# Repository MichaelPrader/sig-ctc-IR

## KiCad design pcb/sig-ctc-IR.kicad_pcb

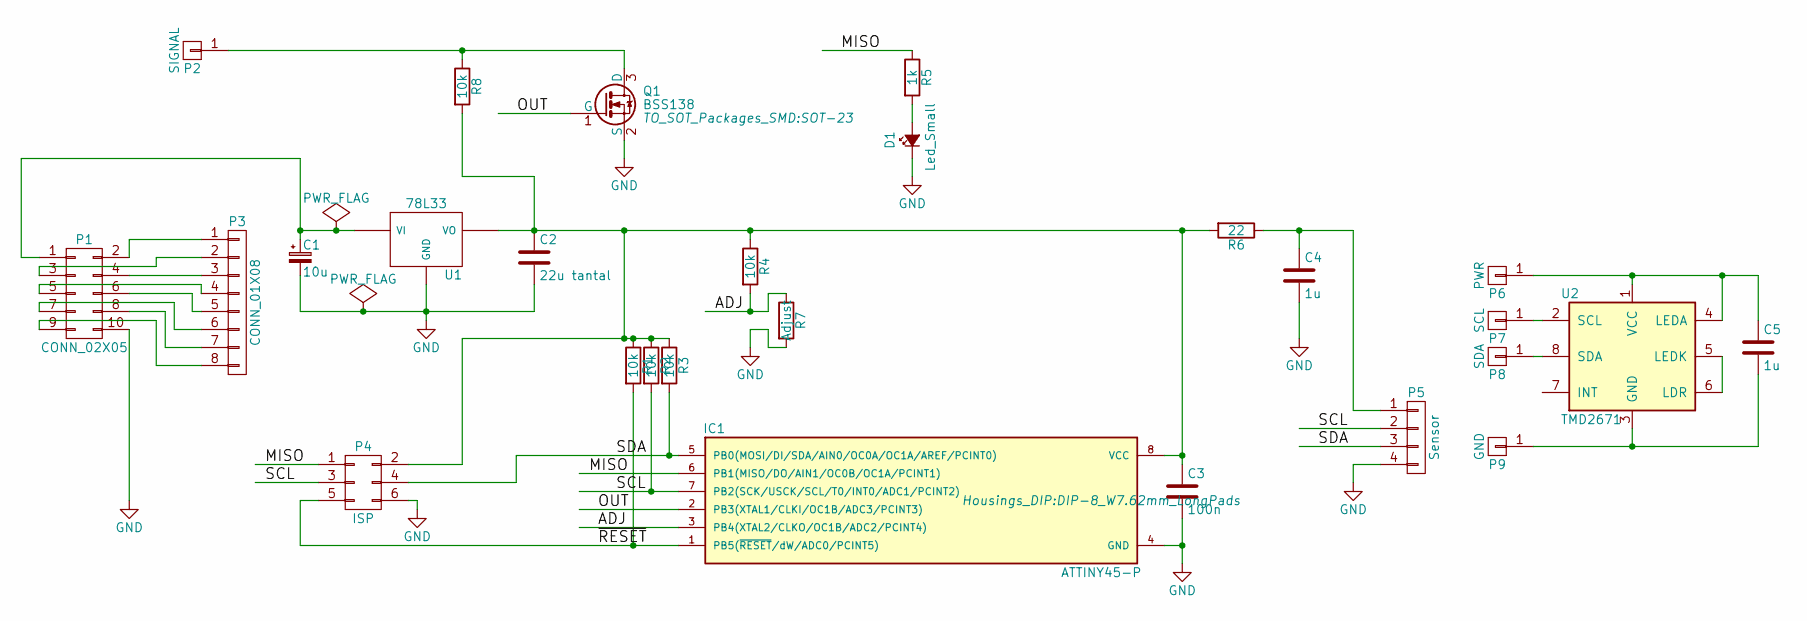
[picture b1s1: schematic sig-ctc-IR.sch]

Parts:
C1: 10u; C_Radial_D5_L6_P2.5
C2: 22u tantal; C_Rect_L7_W2.5_P5
C3: 100n; C_Rect_L7_W2.5_P5
C4, C5: 1u; C_Rect_L7_W2.5_P5
D1: Led_Small; LED-3MM
IC1: ATTINY45-P; DIP-8_W7.62mm_LongPads
P1: CONN_02X05; Pin_Header_Straight_2x05
P2: SIGNAL; Pin_Header_Straight_1x01
P3: CONN_01X08; Pin_Header_Straight_1x08
P4: ISP; Pin_Header_Straight_2x03
P5: Sensor; Pin_Header_Straight_1x04
P6: PWR; SolderWirePad_single_0-8mmDrill
P7: SCL; SolderWirePad_single_0-8mmDrill
P8: SDA; SolderWirePad_single_0-8mmDrill
P9: GND; SolderWirePad_single_0-8mmDrill
Q1: BSS138; SOT-23
R1, R2, R3, R4: 10k; Resistor_Horizontal_RM10mm
R5: 1k; Resistor_Horizontal_RM10mm
R6: 22; Resistor_Horizontal_RM10mm
R7: Adjust; Resistor_Vertical_RM2.5mm
R8: 10k; Resistor_Vertical_RM2.5mm
U1: 78L33; TO-220
U2: TMD2671

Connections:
/ADJ: IC1.3 (PB4(XTAL2/CLKO/OC1B/ADC2/PCINT4)), R4.2, R7.1
/MISO: IC1.6 (PB1(MISO/DO/AIN1/OC0B/OC1A/PCINT1)), P4.1, R5.1
/OUT: IC1.2 (PB3(XTAL1/CLKI/OC1B/ADC3/PCINT3)), Q1.1 (G)
/SCL: IC1.7 (PB2(SCK/USCK/SCL/T0/INT0/ADC1/PCINT2)), P4.3, P5.2, R2.2
/SDA: IC1.5 (PB0(MOSI/DI/SDA/AIN0/OC0A/OC1A/AREF/PCI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), P4.4, P5.3, R3.2
/~RESET: IC1.1 (PB5(~RESET~/dW/ADC0/PCINT5)), P4.5, R1.2
GND: C1.2, C2.2, C3.2, C4.2, D1.1 (K), IC1.4 (GND), P1.10, P4.6, P5.4, Q1.2 (S), R7.2, U1.2 (GND)
unnamed: C1.1, P1.1, U1.1 (VI)
unnamed: C2.1, C3.1, IC1.8 (VCC), P4.2, R1.1, R2.1, R3.1, R4.1, R6.2, R8.2, U1.3 (VO)
unnamed: C4.1, P5.1, R6.1
unnamed: C5.1, P6.1, U2.1 (VCC), U2.4 (LEDA)
unnamed: C5.2, P9.1, U2.3 (GND)
unnamed: D1.2 (A), R5.2
unnamed: P1.2, P3.1
unnamed: P1.3, P3.2
unnamed: P1.4, P3.3
unnamed: P1.5, P3.4
unnamed: P1.6, P3.5
unnamed: P1.7, P3.6
unnamed: P1.8, P3.7
unnamed: P1.9, P3.8
unnamed: P2.1, Q1.3 (D), R8.1
unnamed: P7.1, U2.2 (SCL)
unnamed: P8.1, U2.8 (SDA)
unnamed: U2.5 (LEDK), U2.6 (LDR)

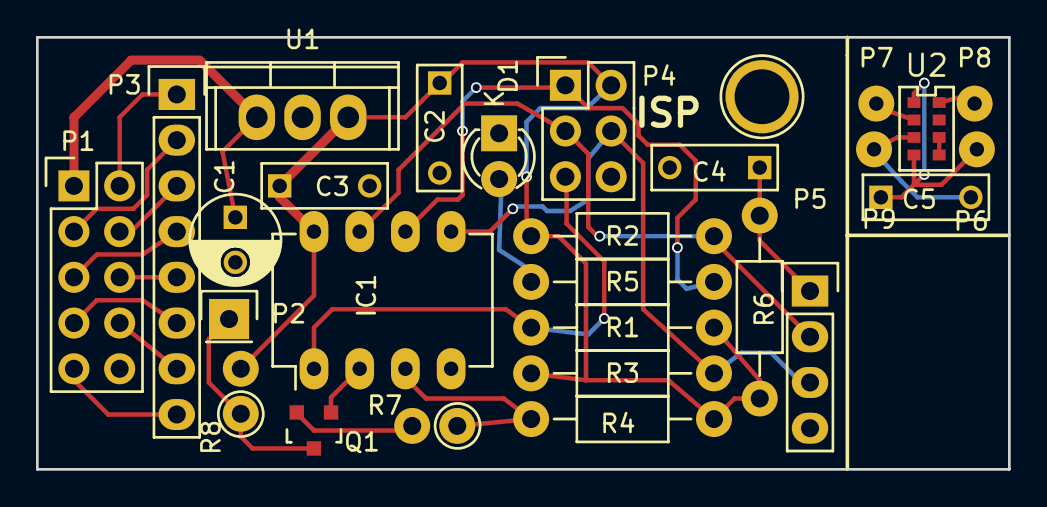
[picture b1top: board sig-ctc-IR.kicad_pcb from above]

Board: 2 copper layers, 54.0 x 24.0 mm, 27 parts (0 on the bottom side), 25 nets.

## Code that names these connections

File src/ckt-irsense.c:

/*************************************************************************
Title:    IR reflective sensor v3.1
Authors:  Michael Petersen <railfan@drgw.net>
          Nathan D. Holmes <maverick@drgw.net>
File:     $Id: $
License:  GNU General Public License v3

LICENSE:
    Copyright (C) 2014 Michael Petersen & Nathan Holmes

    This program is free software; you can redistribute it and/or modify
    it under the terms of the GNU General Public License as published by
    the Free Software Foundation; either version 3 of the License, or
    any later version.

    This program is distributed in the hope that it will be useful,
    but WITHOUT ANY WARRANTY; without even the implied warranty of
    MERCHANTABILITY or FITNESS FOR A PARTICULAR PURPOSE.  See the
    GNU General Public License for more details.

*************************************************************************/

#include <stdlib.h>
#include <avr/io.h>
#include <avr/interrupt.h>
#include <avr/wdt.h>
#include <util/delay.h>

#define   TMD26711_ADDR   0x39
#define   INFO_ADDR       0x20

#define   PROXIMITY_THRESHOLD   0x300
#define   PPULSE_DEFAULT        8

#define   ON_DEBOUNCE_DEFAULT   1

#define   SDA   PB0
#define   SCL   PB2

static inline void sda_low() { DDRB |= _BV(SDA); _delay_us(10); }
static inline void sda_high() { DDRB &= ~_BV(SDA); _delay_us(10); }
static inline void scl_low() { PORTB &= ~_BV(SCL); _delay_us(10); }
static inline void scl_high() { PORTB |= _BV(SCL); _delay_us(10); }

volatile uint8_t ticks;
volatile uint8_t decisecs = 0;

void initialize100HzTimer(void)
{
	// Set up timer 0 for 100Hz interrupts
	TCNT0 = 0;
	OCR0A = 78;  // 8MHz / 1024 / 78 = 100Hz
	ticks = 0;
	decisecs = 0;
	TCCR0A = _BV(WGM01);
	TCCR0B = _BV(CS02) | _BV(CS00);  // 1024 prescaler
	TIMSK |= _BV(OCIE0A);
}

ISR(TIMER0_COMPA_vect)
{
	if (++ticks >= 10)
	{
		ticks = 0;
		decisecs++;
	}
}

void i2cStart(void)
{
	scl_high();
	sda_low();
	scl_low();
	sda_high();
}

void i2cStop(void)
{
	scl_low();
	sda_low();
	scl_high();
	sda_high();
}

uint8_t i2cWriteByte(uint8_t byte)
{
	uint8_t i = 0x80, ack;

	do
	{
		if(byte & i)
		{
			sda_high();
		}
		else
		{
			sda_low();
		}
		
		scl_high();
		scl_low();
		
		i >>= 1;
	} while(i);

	sda_high();  // Release SDA
	
	scl_high();
	if(PINB & _BV(SDA))
		ack = 0;
	else
		ack = 1;
	scl_low();

	return ack;
}

uint8_t i2cReadByte(uint8_t ack)
{
	uint8_t i, data = 0;

	for(i=0; i<8; i++)
	{
		data = data << 1;
		scl_high();
		if(PINB & _BV(SDA))
			data |= 0x01;
		scl_low();
	}
	
	if(ack)
		sda_low();
	scl_high();
	scl_low();
	sda_high();

	return data;
}

uint8_t writeByte(uint8_t addr, uint8_t cmd, uint16_t writeVal)
{
	uint8_t ack;
	
	i2cStart();
	
	i2cWriteByte(addr << 1);
	i2cWriteByte(cmd);
	ack = i2cWriteByte(writeVal);

	i2cStop();

	return ack;
}

uint16_t readWord(uint8_t addr, uint8_t cmd)
{
	uint16_t data;
	
	i2cStart();
	
	i2cWriteByte(addr << 1);
	i2cWriteByte(cmd);

	i2cStart();

	i2cWriteByte((addr << 1) | 0x01);
	data = i2cReadByte(1);
	data |= ((uint16_t)i2cReadByte(0) << 8);
	
	i2cStop();

	return data;
}

void init(void)
{
	MCUSR = 0;
	wdt_reset();
	wdt_enable(WDTO_250MS);
	wdt_reset();

	// Configure ADC
	ADMUX = 0x02;  // ref = VCC, right-justified, input = PB4 (ADC2)
	ADCSRA = 0x87; // ADC enabled, prescaler = 128
	DIDR0 = _BV(ADC2D);  // Disable ADC2 digital input buffer
	
	PORTB = _BV(SCL) | _BV(PB1);  // All outputs low except SCL and PB1
	DDRB |= _BV(PB1) | _BV(SCL) | _BV(PB3);
}

int main(void)
{
	uint16_t proximity;
	uint8_t detect = 0;
	uint16_t count = 0;  // 256 decisecs * 60 (long delay mode) = 15360 max count
	uint8_t ppulse;
	int16_t adc, adc_filt = 0;
	int16_t on_debounce, off_debounce;  // Signed so the math for off_debounce doesn't wrap
	
	// Application initialization
	init();
	initialize100HzTimer();
	sei();

	// Initialize TMD26711 (bit 0x80 set to indicate command)
	writeByte(TMD26711_ADDR, 0x80|0x00, 0x00);   // Start with everything disabled
	writeByte(TMD26711_ADDR, 0x80|0x01, 0xFF);   // Minimum ATIME
	writeByte(TMD26711_ADDR, 0x80|0x02, 0xFF);   // Maximum integration time
	writeByte(TMD26711_ADDR, 0x80|0x03, 0xFF);   // Minimum wait time
	
	// Note: IRQ not currently used
	writeByte(TMD26711_ADDR, 0x80|0x08, 0x00);   // Set interrupt low threshold to 0x0000
	writeByte(TMD26711_ADDR, 0x80|0x09, 0x00);
	writeByte(TMD26711_ADDR, 0x80|0x0A, 0x00);   // Set interrupt low threshold to 0x0300
	writeByte(TMD26711_ADDR, 0x80|0x0B, 0x03);
	writeByte(TMD26711_ADDR, 0x80|0x0C, 0x10);   // Single out-of-range cycle triggers interrupt

	writeByte(TMD26711_ADDR, 0x80|0x0D, 0x00);   // Long wait disabled
	writeByte(TMD26711_ADDR, 0x80|0x0E, PPULSE_DEFAULT); // Pulse count
	writeByte(TMD26711_ADDR, 0x80|0x0F, 0x20);   // 100% LED drive strength, Use channel 1 diode (ch 1 seems less sensitive to fluorescent light)

	writeByte(TMD26711_ADDR, 0x80|0x00, 0x27);   // Power ON, Enable proximity, Enable proximity interrupt (not used currently)

	while (1)
	{
		wdt_reset();

		if(decisecs >= 1)
		{
			decisecs = 0;

			ppulse = PPULSE_DEFAULT;
			writeByte(TMD26711_ADDR, 0x80|0x0E, ppulse);

			// Read ADC
			ADCSRA |= _BV(ADSC);  // Trigger conversion
			while(ADCSRA & _BV(ADSC));
			adc = ADC;
			adc_filt = adc_filt + ((adc - adc_filt) / 4);

			on_debounce = ON_DEBOUNCE_DEFAULT;
			off_debounce = ((1023 - adc_filt) - 100 + 2) / 4;  // Invert, shift, divide-by-4, round
			if(off_debounce < 1)
				off_debounce = 1;  // Limit to 1
#ifdef LONG_DELAY
			off_debounce *= 60;
#endif
			// Telemetry
			writeByte(INFO_ADDR, adc_filt >> 8, adc_filt & 0xFF);

			proximity = readWord(TMD26711_ADDR, 0x80|0x20|0x18);  // Read data register (0x80 = command, 0x20 = auto-increment)

			if(!detect & (proximity >= PROXIMITY_THRESHOLD))
			{
				// ON debounce
				count++;
				if(count > on_debounce)
				{
					detect = 1;
					count = 0;
				}
			}
			else if(!detect & (proximity < PROXIMITY_THRESHOLD))
			{
				count = 0;
			}

			else if(detect & (proximity < PROXIMITY_THRESHOLD))
			{
				// OFF debounce
				count++;
				if(count > off_debounce)
				{
					detect = 0;
					count = 0;
				}
			}
			else if(detect & (proximity >= PROXIMITY_THRESHOLD))
			{
				count = 0;
			}
		}

		if(detect)
		{
			PORTB |= _BV(PB3);
			PORTB &= ~_BV(PB1);
		}
		else
		{
			PORTB &= ~_BV(PB3);
			PORTB |= _BV(PB1);
		}
	}
}

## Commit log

2017-06-03 checkin
